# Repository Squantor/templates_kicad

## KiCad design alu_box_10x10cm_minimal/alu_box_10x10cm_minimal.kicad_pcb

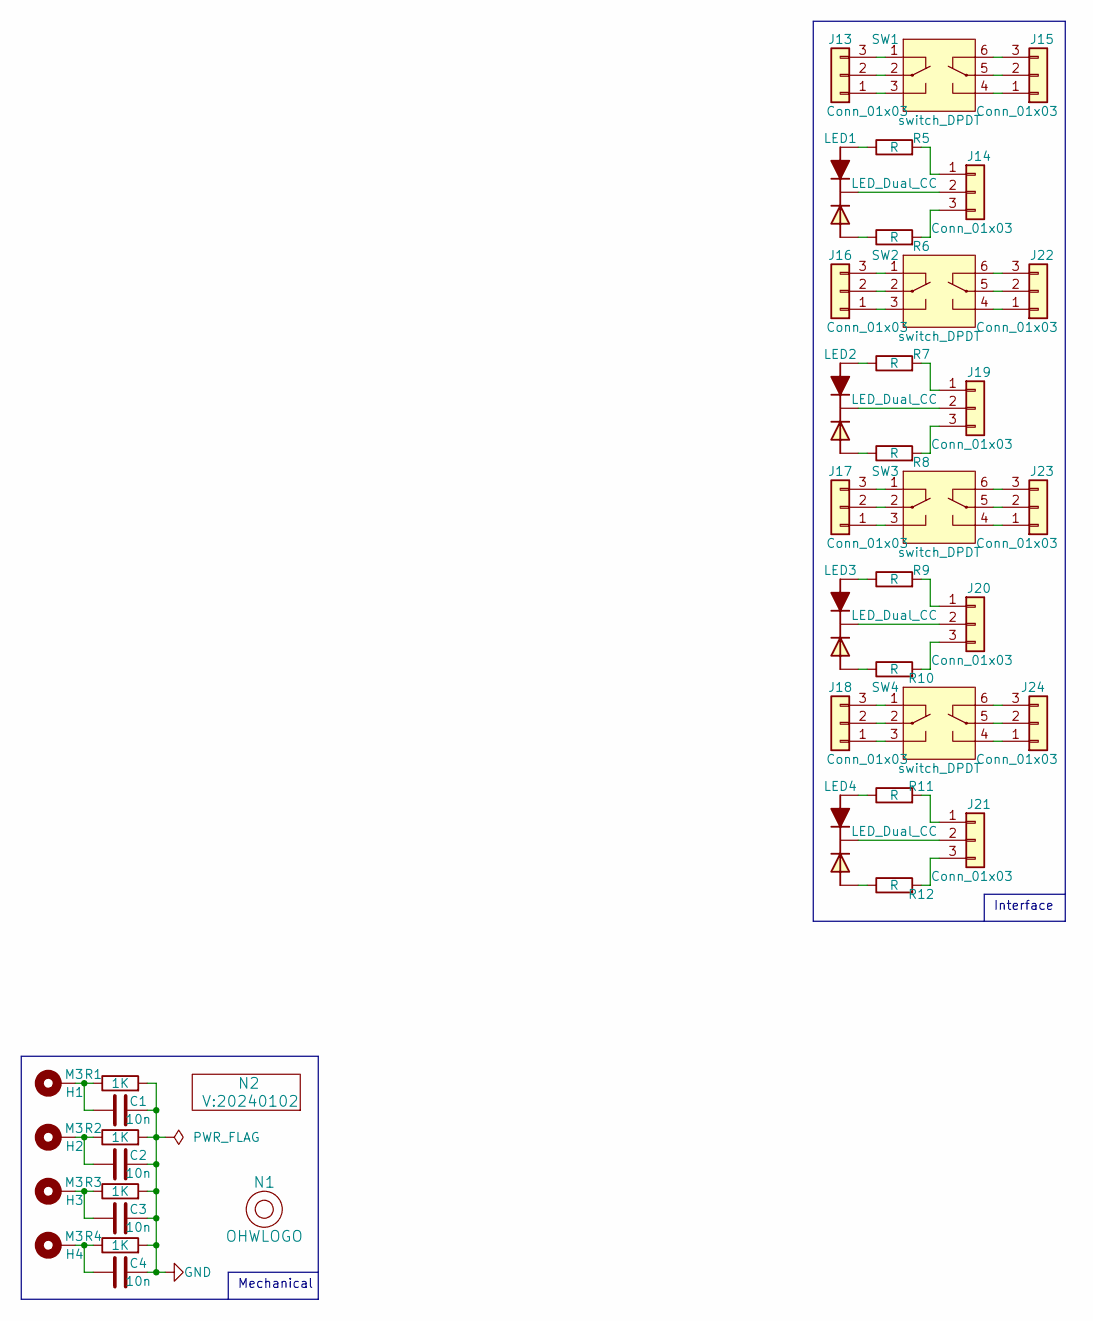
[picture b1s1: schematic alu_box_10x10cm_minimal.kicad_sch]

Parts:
C1, C2, C3, C4: 10n; C_0805+0603
H1, H2, H3, H4: M3; MountingHole_3.2mm_M3_Pad_Via
J13, J14, J15, J16, J17, J18, J19, J20, J21, J22, J23, J24: Conn_01x03; JST_PH_B3B-PH-K_1x03_P2.00mm_Vertical
LED1, LED2, LED3, LED4: LED_Dual_CC; LED_DUAL_TH245_90deg
N1: OHWLOGO; OSHW-Symbol_6.7x6mm_SilkScreen
N2: V:20240102; Label_Generic
R1, R2, R3, R4: 1K; R_0805+0603
R5, R6, R7, R8, R9, R10, R11, R12: R; R_0603_hand
SW1, SW2, SW3, SW4: switch_DPDT; PS-22F02

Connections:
GND: C1.2, C2.2, C3.2, C4.2, R1.2, R2.2, R3.2, R4.2
unnamed: C1.1, H1.1, R1.1
unnamed: C2.1, H2.1, R2.1
unnamed: C3.1, H3.1, R3.1
unnamed: C4.1, H4.1, R4.1
unnamed: J13.1, SW1.3 (SW1_P2)
unnamed: J13.2, SW1.2 (SW1_C1)
unnamed: J13.3, SW1.1 (SW1_P1)
unnamed: J14.1, R5.2
unnamed: J14.2, LED1.2 (C)
unnamed: J14.3, R6.2
unnamed: J15.1, SW1.4 (SW2_P2)
unnamed: J15.2, SW1.5 (SW2_C1)
unnamed: J15.3, SW1.6 (SW2_P2)
unnamed: J16.1, SW2.3 (SW1_P2)
unnamed: J16.2, SW2.2 (SW1_C1)
unnamed: J16.3, SW2.1 (SW1_P1)
unnamed: J17.1, SW3.3 (SW1_P2)
unnamed: J17.2, SW3.2 (SW1_C1)
unnamed: J17.3, SW3.1 (SW1_P1)
unnamed: J18.1, SW4.3 (SW1_P2)
unnamed: J18.2, SW4.2 (SW1_C1)
unnamed: J18.3, SW4.1 (SW1_P1)
unnamed: J19.1, R7.2
unnamed: J19.2, LED2.2 (C)
unnamed: J19.3, R8.2
unnamed: J20.1, R9.2
unnamed: J20.2, LED3.2 (C)
unnamed: J20.3, R10.2
unnamed: J21.1, R11.2
unnamed: J21.2, LED4.2 (C)
unnamed: J21.3, R12.2
unnamed: J22.1, SW2.4 (SW2_P2)
unnamed: J22.2, SW2.5 (SW2_C1)
unnamed: J22.3, SW2.6 (SW2_P2)
unnamed: J23.1, SW3.4 (SW2_P2)
unnamed: J23.2, SW3.5 (SW2_C1)
unnamed: J23.3, SW3.6 (SW2_P2)
unnamed: J24.1, SW4.4 (SW2_P2)
unnamed: J24.2, SW4.5 (SW2_C1)
unnamed: J24.3, SW4.6 (SW2_P2)
unnamed: LED1.1 (A1), R5.1
unnamed: LED1.3 (A2), R6.1
unnamed: LED2.1 (A1), R7.1
unnamed: LED2.3 (A2), R8.1
unnamed: LED3.1 (A1), R9.1
unnamed: LED3.3 (A2), R10.1
unnamed: LED4.1 (A1), R11.1
unnamed: LED4.3 (A2), R12.1

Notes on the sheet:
Interface
Mechanical

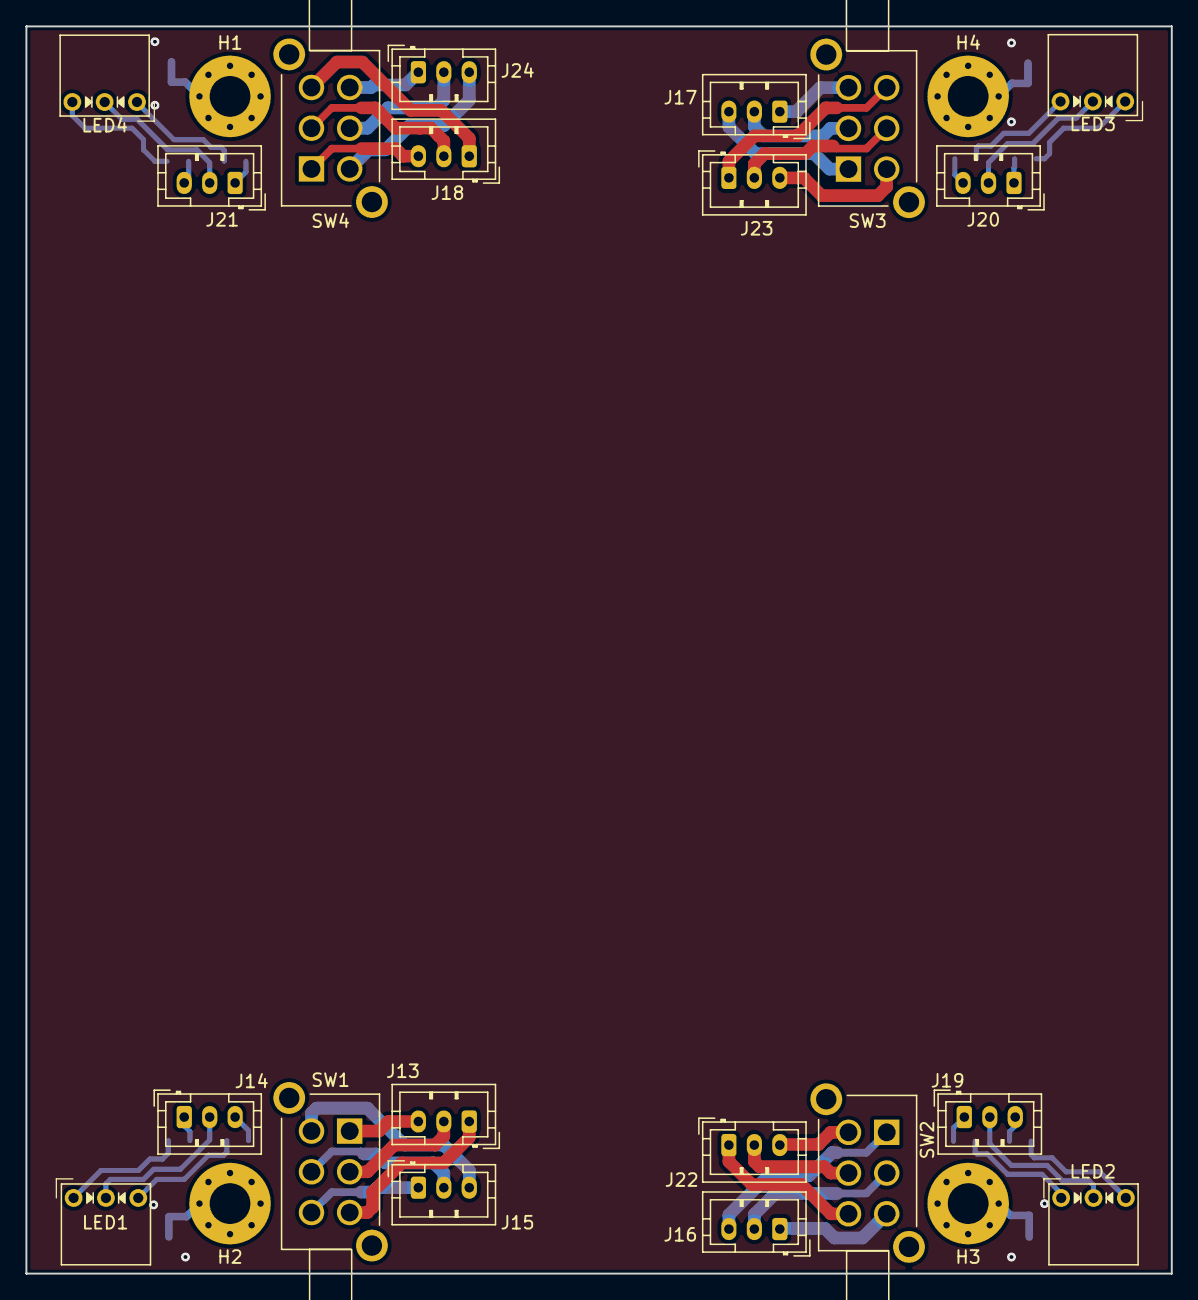
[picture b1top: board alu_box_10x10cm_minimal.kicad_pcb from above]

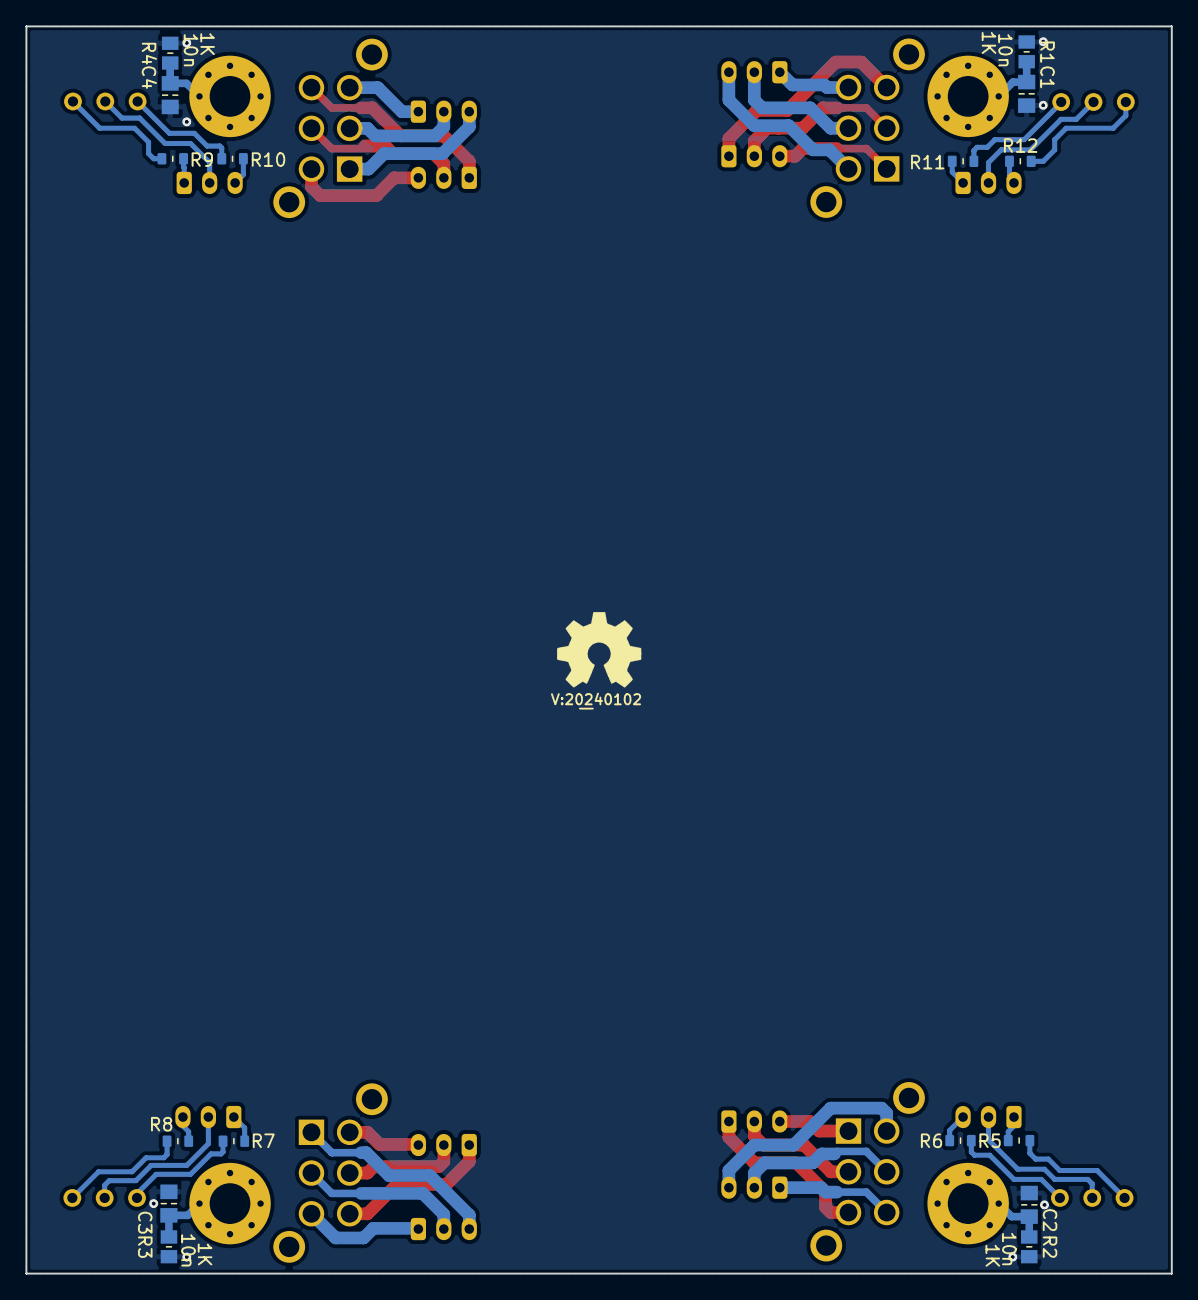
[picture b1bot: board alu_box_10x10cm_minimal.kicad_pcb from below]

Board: 2 copper layers, 90.0 x 98.0 mm, 42 parts (18 on the bottom side), 49 nets.
